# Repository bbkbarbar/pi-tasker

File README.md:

# Control center in living room
Based on Raspberry Pi Zero

#### Clients can get infos from:
###### - Environment:
 	- Air temperature
 	- Aquarium-water temperature
 	- Relative humidity (later)
###### - Internal status:
 	- Worker info (contains toDo items)
 	- Pwm output stated
 	- IO output states
###### - System infos
 	- CPU temp
 	- Memory info (later if needed)
 	- Free space (later if needed)
 	- Network logs (# of connections, etc.) (later if needed)

#### Temperature warnings can be sent via email for multiple recipient in case of:
  - temperature (in selected sensor) rises above specified limit
  - temperature (in selected sensor) drops below specified limit

Temperature warning rules described in [JSON file](https://github.com/bbkbarbar/pi-tasker/blob/master/onTarget/home_-_pi/taskerData/TempWarnings.json).

#### Client can control:
| Item           | Control type               | Scheduled | Sensor based control | Exceptional control | Src                      |
| :------------- | :------------------------: | :-------: | :------------------: | :-----------------: | :----------------------: |
| Airpump        | On/Off                     | X         | -                    | X                   | 230VAC                   |
| Filter         | On/Off                     | X         | -                    | X                   | 230VAC                   |
| Water heater   | On/Off                     | X         | X                    | X                   | 230VAC                   |
| Water cooler   | Gradual speed control (pwm)| X         | X                    | X                   | 230VAC->12VDC - 1ch pwm  |
| Light          | On/Off, 3ch RGB color      | X         | -                    | X                   | 230VAC->12VDC - 3ch pwm  |

Note: System can handle further pwm output (in fact unlimited number / just depends on how much devices do you have from [Serial PWM Driver](https://bbkbarbar.github.io/Serial_PWM_Driver_with_OLED)).

[For furher information follow t link](https://bbkbarbar.github.io/Serial_PWM_Driver_with_OLED/#further_channels)

#### Other outputs:
 - WebUI (show temperature infos and status infos of controller peripherials)
 - Temperature logs
 - System logs

## Used external tool(s):
 - Install Apache Webserver:
 ```
 sudo apt-get install apache2 -y
 ```

## Deployment
 - Copy content of onTarget folder to user's folder on target.
 - Run deploy script (deploy.sh)
 - Copy release to user's folder
 - run first with run.sh with name of copied release as parameter (./run.sh t102.jar)

## Wireing
  Planned connection modul, to make connection clean:
  
  Note: Pi Zero has some GND and VCC pins in GPIO port, but more external module need to get power from Pi. Previously I tried to give energy for a module from output of an other, but this makes the connections complex.<br>
  So I'm planning to create a "connector" module (something like above), to make connections clean and clear.

## ToDo list:
 - [ ] Cleanup files for easy deployment
 - [ ] Create "deploy script"

[Back to top](#top)

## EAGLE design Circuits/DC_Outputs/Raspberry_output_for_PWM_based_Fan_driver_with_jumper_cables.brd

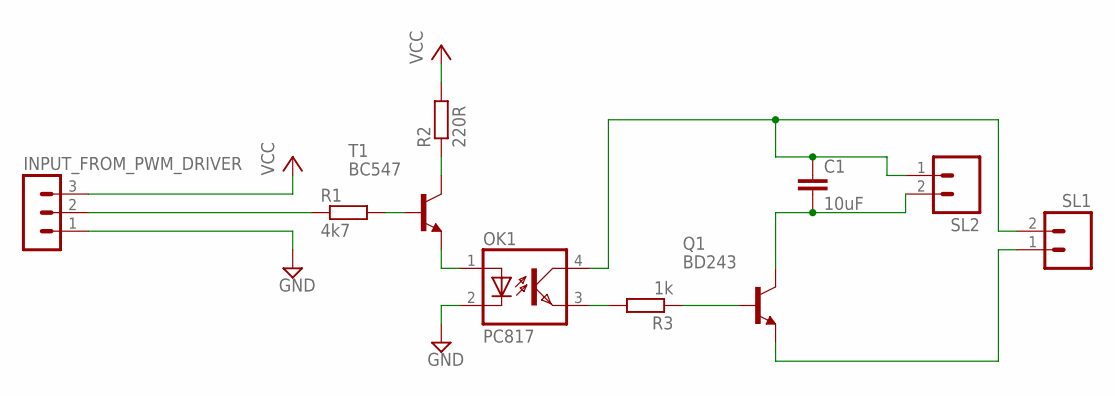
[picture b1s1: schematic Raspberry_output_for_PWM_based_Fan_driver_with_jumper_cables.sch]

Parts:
C1: 10uF; C2.5-5
INPUT_FROM_PWM_DRIVER: MA03-1
OK1: PC817; DIL04
Q1: BD243; TO220
R1: 4k7; 0207/10
R2: 220R; 0207/10
R3: 1k; 0207/10
SL1, SL2: MA02; 02PA
T1: BC547; TO92

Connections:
GND: INPUT_FROM_PWM_DRIVER.1, OK1.2 (C)
INPUT: INPUT_FROM_PWM_DRIVER.2, R1.1
INPUT_REGULATED_CURR_2_BASE: R1.2, T1.2 (B)
unnamed: R2.1, T1.3 (C)
OPTO_IN: OK1.1 (A), T1.1 (E)
OPTO_OUT_2_TR: OK1.3 (EMIT), R3.2
OUTPUT_N: C1.2, Q1.2 (C), SL2.2
SOURCE_N_0V: Q1.3 (E), SL1.1
SOURCE_P_12V: C1.1, OK1.4 (COL), SL1.2, SL2.1
TR_OUTPUT_BASE: Q1.1 (B), R3.1
VCC: INPUT_FROM_PWM_DRIVER.3, R2.2

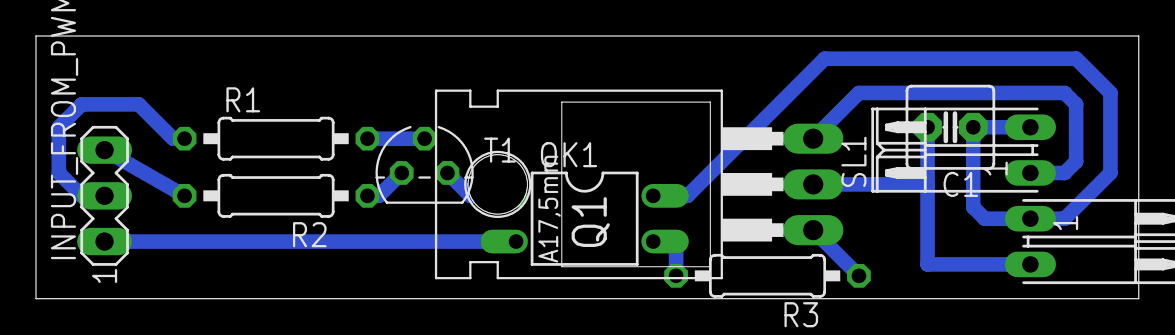
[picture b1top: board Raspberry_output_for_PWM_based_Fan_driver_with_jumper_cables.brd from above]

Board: 2 copper layers, 61.3 x 14.6 mm, 10 parts (0 on the bottom side), 11 nets.

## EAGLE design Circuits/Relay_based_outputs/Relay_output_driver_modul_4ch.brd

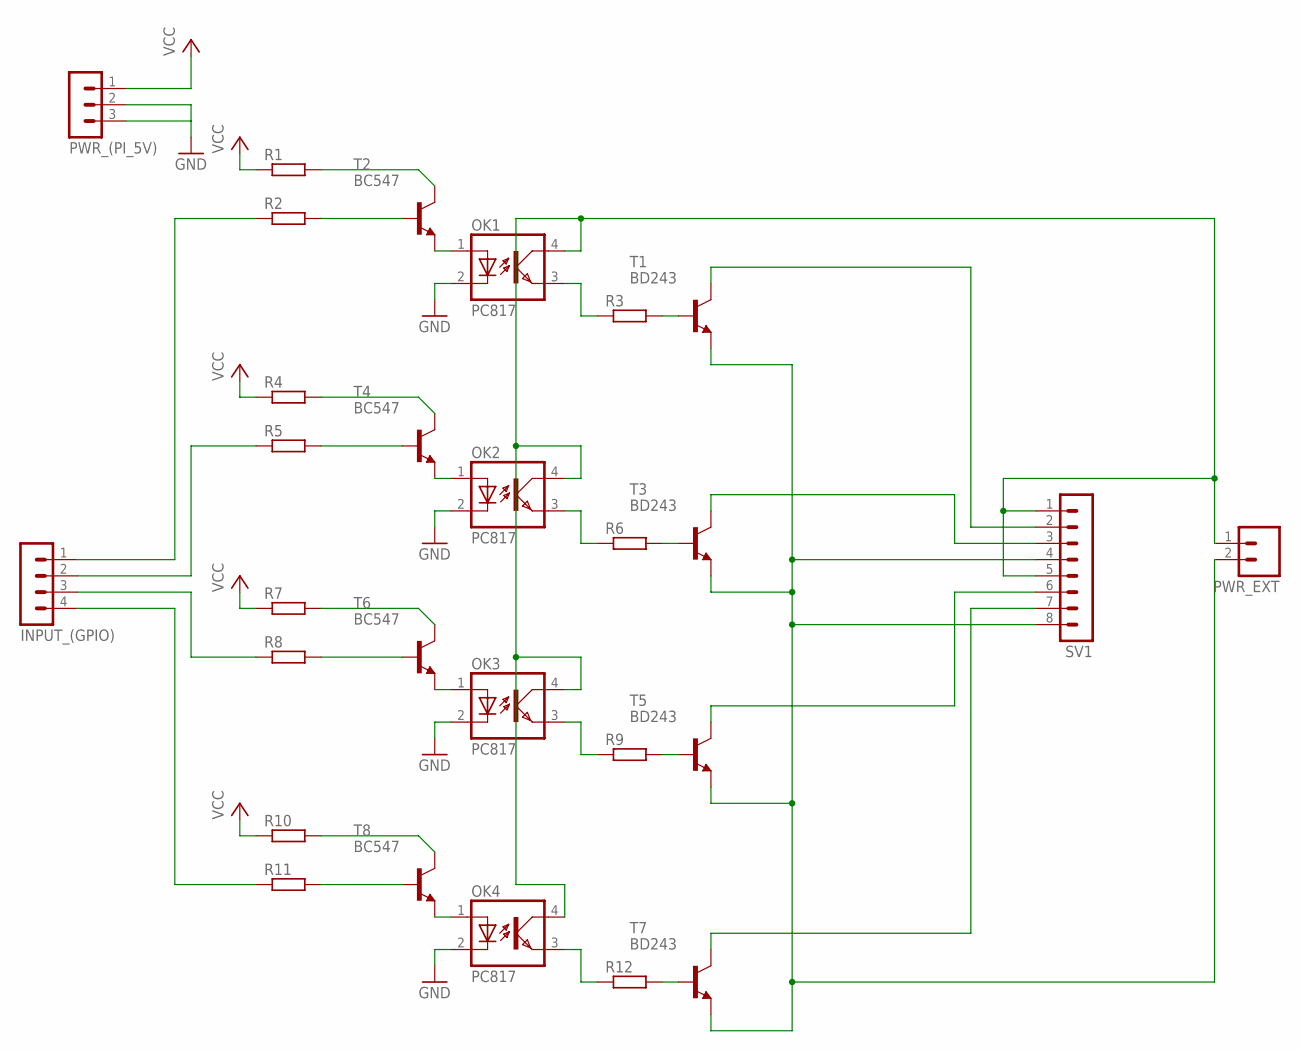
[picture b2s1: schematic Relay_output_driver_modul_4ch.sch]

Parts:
INPUT_(GPIO): MA04-1
OK1, OK2, OK3, OK4: PC817; DIL04
PWR_(PI_5V): MA03-1
PWR_EXT: MA02; 02PA
R1, R2, R3, R4, R5, R6, R7, R8, R9, R10, R11, R12: R-EU_0207/10; 0207/10
SV1: MA08-1
T1, T3, T5, T7: BD243; TO220
T2, T4, T6, T8: BC547; TO92

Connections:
GND: OK1.2 (C), OK2.2 (C), OK3.2 (C), OK4.2 (C), PWR_(PI_5V).2, PWR_(PI_5V).3
INPUT_1: INPUT_(GPIO).1, R2.1
INPUT_2: INPUT_(GPIO).2, R5.1
INPUT_3: INPUT_(GPIO).3, R8.1
INPUT_4: INPUT_(GPIO).4, R11.1
unnamed: OK1.1 (A), T2.1 (E)
unnamed: R3.2, T1.1 (B)
unnamed: OK1.3 (EMIT), R3.1
unnamed: R2.2, T2.2 (B)
unnamed: R1.2, T2.3 (C)
unnamed: OK2.1 (A), T4.1 (E)
unnamed: R6.2, T3.1 (B)
unnamed: OK2.3 (EMIT), R6.1
unnamed: R5.2, T4.2 (B)
unnamed: R4.2, T4.3 (C)
unnamed: OK3.1 (A), T6.1 (E)
unnamed: R9.2, T5.1 (B)
unnamed: OK3.3 (EMIT), R9.1
unnamed: R8.2, T6.2 (B)
unnamed: R7.2, T6.3 (C)
unnamed: OK4.1 (A), T8.1 (E)
unnamed: R12.2, T7.1 (B)
unnamed: OK4.3 (EMIT), R12.1
unnamed: R11.2, T8.2 (B)
unnamed: R10.2, T8.3 (C)
OUTPUT_1: SV1.2, T1.2 (C)
OUTPUT_2: SV1.3, T3.2 (C)
OUTPUT_3: SV1.6, T5.2 (C)
OUTPUT_4: SV1.7, T7.2 (C)
PWR_EXT_5V: OK1.4 (COL), OK2.4 (COL), OK3.4 (COL), OK4.4 (COL), PWR_EXT.1, SV1.1, SV1.5
PWR_EXT_GND: PWR_EXT.2, SV1.4, SV1.8, T1.3 (E), T3.3 (E), T5.3 (E), T7.3 (E)
VCC: PWR_(PI_5V).1, R1.1, R4.1, R7.1, R10.1

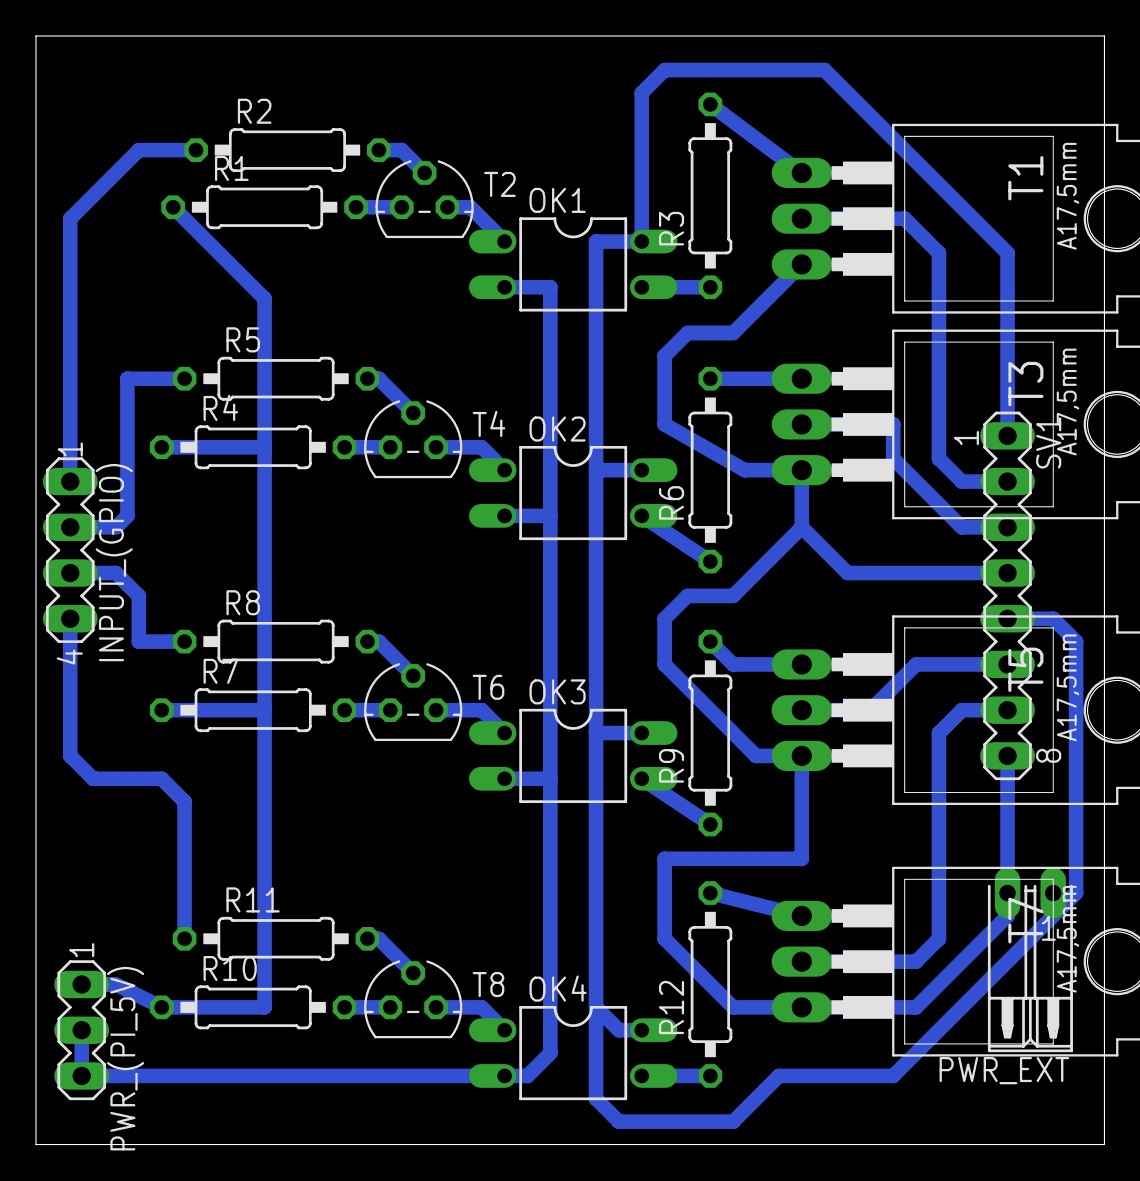
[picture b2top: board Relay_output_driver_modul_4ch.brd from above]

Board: 2 copper layers, 59.4 x 61.6 mm, 28 parts (0 on the bottom side), 32 nets.

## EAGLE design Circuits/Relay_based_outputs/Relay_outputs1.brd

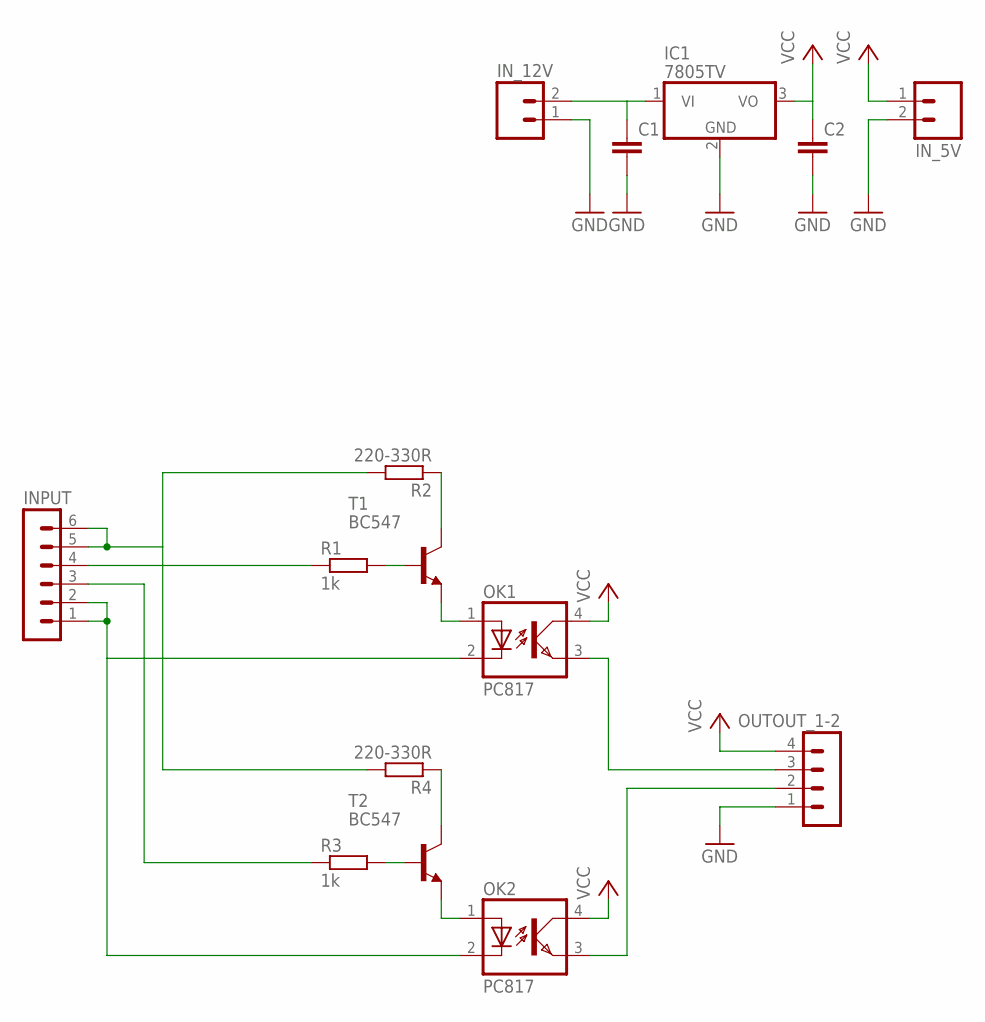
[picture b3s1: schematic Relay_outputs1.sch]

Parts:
C1, C2: C-EU050-024X044; C050-024X044
IC1: 7805TV; TO220V
INPUT: MA06-1
IN_5V, IN_12V: MA02; 02PA
OK1, OK2: PC817; DIL04
OUTOUT_1-2: MA04-1
R1, R3: 1k; 0207/10
R2, R4: 220-330R; 0207/10
T1, T2: BC547; TO92

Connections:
DC_IN: C1.1, IC1.1 (VI), IN_12V.2
GND: C1.2, C2.2, IC1.2 (GND), IN_5V.2, IN_12V.1, OUTOUT_1-2.1
INPUT_REGULATED_CURR_2_BASE: R1.2, T1.2 (B)
INPUT_REGULATED_CURR_2_BASE1: R3.2, T2.2 (B)
unnamed: R2.1, T1.3 (C)
unnamed: R4.1, T2.3 (C)
OPTO_IN: OK1.1 (A), T1.1 (E)
OPTO_IN1: OK2.1 (A), T2.1 (E)
OUT1: OK1.3 (EMIT), OUTOUT_1-2.3
OUT2: OK2.3 (EMIT), OUTOUT_1-2.2
PI_GND: INPUT.1, INPUT.2, OK1.2 (C), OK2.2 (C)
PI_OUT_1: INPUT.4, R1.1
PI_OUT_2: INPUT.3, R3.1
PI_VCC: INPUT.5, INPUT.6, R2.2, R4.2
VCC: C2.1, IC1.3 (VO), IN_5V.1, OK1.4 (COL), OK2.4 (COL), OUTOUT_1-2.4

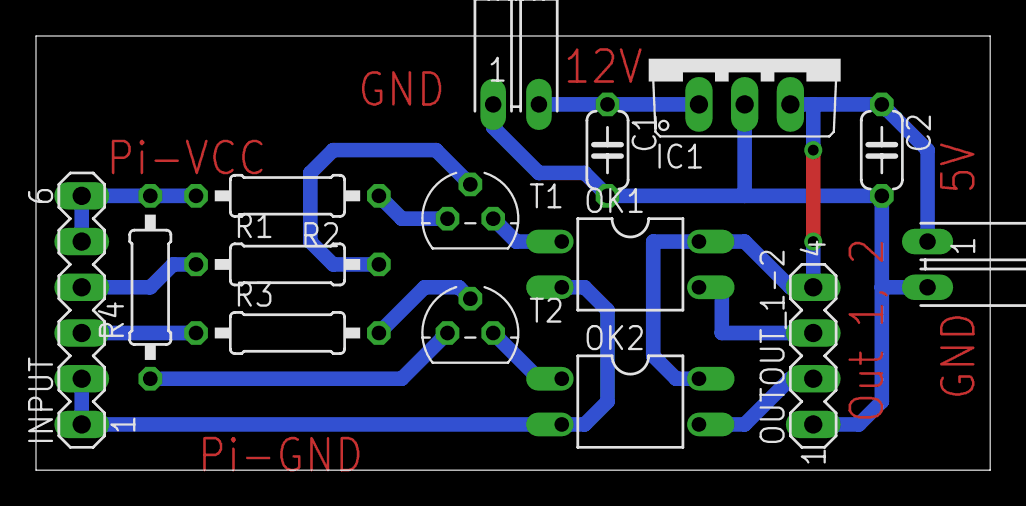
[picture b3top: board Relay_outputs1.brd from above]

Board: 2 copper layers, 53.0 x 24.1 mm, 15 parts (0 on the bottom side), 15 nets.

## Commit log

2016-08-14 commit to dedicated repo
2016-08-14 Refactor
2016-08-14 GitIgnore added
2016-08-14 copy files from old repo
2016-08-14 Communication classed refactored
2016-08-14 Works as a maven project
2016-08-16 TempControllers loaded from Json
2016-08-18 HotFix, need to find problem
2016-08-24 Add circuit design for detached low current relay-module controller
2016-08-27 Minimal modifications
2016-08-30 Create final circuit design for Fan controller and relay driver modules
2016-08-30 Circuit and PCB design added for fan driver module
    Based on jumper-cable -connections
2016-08-30 only test-only modification - removed
2016-09-04 Get IO state -function added (b#82)
2016-09-05 Can receive "get state of" commands, But not send response yet.
2016-09-05 Pinput config can handle "reversed IO" -like configurations
2016-09-05 Function: get state of ... seems OK except the "reversed" feature
2016-09-05 Get state of function mainly works
    except the "Reverse" function
2016-09-05 Get state of ... function seems OK
2016-09-05 Add feature: get state of ...
2016-09-05 Get state of ... works (with reversed IO outputs too)
2016-09-05 Get state of .. WORKS properly (with reversed output too)
2016-09-05 Warnings fixed.
2016-09-06 Use StateMsg object as response of "get state of ..." request
2016-09-06 SafetySwichOff - added (partly done)
2016-09-06 Response of "get state of ..." request sent as StatusMsg object
2016-09-08 Fan boost start parameters load from baseconfig
2016-09-08 Add parameters of fan boost start -function to base.conf
2016-09-09 Json formatting
2016-09-09 TempController related config file udated
2016-09-10 Update project specification
2016-09-11 Worker can get list of toDoItems
2016-09-11 TempWarnings (mulitple) can be loaded from 1 JSON file.
2016-09-11 Add sample JSON for TempWarnings
2016-09-11 TempWarning JSON file show as link
2016-09-11 Remove old test-only file
2016-09-11 bug fix
2016-09-11 Function added: getDirectionAsHuman
2016-09-11 Direction can described "as human" (below/above) instead of -1/+1.
2016-09-11 Use human-readable direction and observedSensor values
2016-09-11 TempControl's output does not contains "RuleID" if there is only 1 rule.
2016-09-11 Add sample for tempWarning.json
2016-09-12 Do not show RuleID if there is only 1 rule
2016-09-12 Debug level changed to INFO.
2016-09-12 Add EventLogger entries
2016-09-12 Clean commented parts
2016-09-12 Backup of -before cleaning- Tasker.java
2016-09-12 EventLogger get "Turn Off (heater/cooler)" event.
2016-09-14 Add function: getHumidityOnly (with mocked reader script)
2016-09-14 Can read and send humidity value
2016-09-14 Read humidity (with mock yet)
2016-09-19 Pinout config can saved as JSON.
2016-09-22 Works from ini conf, can test json conf
2016-09-28 HeaterLogItem added.
2016-09-30 HeaterLogItem added with tests
2016-10-01 Remove unnecessary code parts.
2016-10-01 Rename HeaterLog -> UseageLog
2016-10-01 Add UseageLog and UseageLogItem classes
2016-10-01 Package refactor only
2016-10-01 Name refactor
2016-10-01 TempController can provide energyConsumptionInfo if UsageLog added.
2016-10-01 Add energyConsumptionInfo
2016-10-02 Heater usage log seems OK.
2016-10-24 Reading humidity works fine.
2016-10-29 Map to humidity reader script changed to mocked.
2016-11-25 Add json to define timed output events
2016-11-25 Add feature for scheduled output events
2016-11-25 Add some log info
2016-11-28 Fix issue: multiple pwm channel update
2016-11-28 update JSON
2016-11-29 b96 - working version
2016-12-17 Try to solve bug in OutputState's constuctor
2017-02-10 Set theme jekyll-theme-slate
2017-02-27 Remove unsused lines
2017-02-27 Pack eagle files as .zip
2017-02-28 Minimal refactor near external resouces
2017-03-01 Add currently used external resources
2017-03-01 Pack contained .js files as .zip
2017-03-02 Fix invalide JSON
2017-03-02 remove temporary test lines
2017-03-09 Update filenames according to live version
2017-03-10 Decrease log level of humidity reading - t99
2017-03-24 live/io.py renamed because of Python-Serial-ISSUE
2017-03-24 Disable temperature related ToDoItems
2017-03-24 get LogLevels from JSON; temperature reading mocked.
2017-03-25 PWM outputs works fine with Serial-PWM-Driver
2017-03-25 Add misc files for Pi-user's folder
2017-03-25 Add instruction for install used webserver service
2017-03-25 Add Releases folder to store last builds
2017-03-25 Move file to appropira folder
2017-03-25 Add ToDo list
2017-03-25 update onBoard taskDate folder
2017-03-25 cleanup file-structure
2017-03-25 Add deploy script
2017-03-26 Update light values (sunrise / sunset)
2017-03-27 DayLightSavingTime -issue of ScheduledOutputEvent solved. - Need to test on target device
2017-03-27 Add script for cloning deployment content only
2017-03-27 DayLightSavingTime -issue of ScheduledOutputEvent solved. - Need to test
2017-03-27 Reaf logLevels from multi-level JSON config
2017-03-27 Add skeleton of mail.config
2017-03-27 Add missing config file
2017-03-27 Add latest build
2017-03-27 DayLightTimeZone Issue solved
2017-03-27 Restore outputConfig.json
2017-03-28 Current running version
2017-03-28 Add error-logs for read-int-from-json parts, to find the source of problem
2017-03-29 Modify pom for build runnable jar with Maven install
2017-03-29 Output config reading issue solved
2017-03-29 Add exception handling and readable log messages when IOLogger, EventLogger or Mailer can not be initialized due missing config
2017-03-29 Some fixing + Start to implement using any value from configJSON
2017-03-29 Tests added for reading single- and multi-level configValues from ConfigJSON
2017-03-29 Add sample JSONs for testing and for normal sample
2017-03-29 Config can read values from multi-level JSON-path
2017-03-29 Config can be loaded from JSON
2017-03-29 Add unnamed build to gitIgnore
2017-03-29 Fix typos
2017-03-29 Config values can be loaded from config JSON
2017-03-29 Read configs from JSON works - b107
2017-03-29 Rename last build
2017-03-30 Add sample for scheduledOutputEvents.json
2017-03-30 Update scheduled output events to create sunset of fishtank
2017-03-30 Add calculator to create sunset/sunrise easily
2017-03-30 Refactor since there is no t(String) method in Logger
2017-03-30 Add javadoc for getConfig..() methods
2017-03-30 Typo fix
2017-03-30 Refactor config loading, use config elements from JSON
2017-03-31 BuildNumber moved to a separated class for clear git history
2017-03-31 TempLogger instances reads their parameters from config JSON
2017-03-31 Read path for IO and Event logs from config JSON
2017-03-31 WebUI can read temperature log feed and write own log for different log folder. It uses the temp_logger.path_for_logfile parameter for the feed
2017-03-31 App can run again on local device too
2017-03-31 Update sample JSONs
2017-03-31 Initialize main Logger instance with parameters from baseConfig.json
2017-03-31 Default PATH_FOR_LOG_FOLDER will works on target and on dev environment too
2017-03-31 Implament function guaranteePathSeparatorAtEndOf to make code cleaner
2017-03-31 Guarantee slash at the end of folder path moved to FileHandler
2017-03-31 Method getInt() implemented in Config class
2017-03-31 Parameter: fan start boost time in ms moved to baseConfig.json
2017-03-31 Refactor: Config.getConfig.. -> Config.get...
2017-03-31 All parameters from old base.conf moved to baseConf.json
2017-03-31 All config parameters loaded from baseConf.json
2017-03-31 Clean onTarget taskerData folder. Removed non-used config files
2017-03-31 Refactor, remove uneccesarry lines
2017-03-31 Refactor methods what uses the old base.conf
2017-03-31 Solve warnings
2017-03-31 Heater's energy consumption can be loaded from baseConfig.json; We can read Floats and Doubles from config JSON
2017-03-31 Add heater's energy consumption as part of baseConfig
2017-03-31 Update mvn site with project infos
2017-03-31 update since scheudled RGB lighting works fine
2017-03-31 Filename for basic temperature log can be loaded from config JSON
2017-03-31 Can read Objects from any JSON like from baseConfig.json
2017-03-31 Add missing log-case in tempWarning class
2017-03-31 Path of live web content loaded from config json
2017-03-31 Mailer gives more reable log messages if it can not be initialized
2017-03-31 Can run n dev-env, need to try out on target device
2017-04-01 Add funciton fixPathSeparator (for current OS)
2017-04-02 Normalize log-levels for read pinout config -funciton
2017-04-02 Everithing seems OK.
2017-04-02 Rename String-type Config.get(..) functions as getString(..)
2017-04-02 Implement function: Config.getArray(..) to read JSONArray from config.json
2017-04-02 Add unitTest for readOutputConfigFromIni(..)
2017-04-02 OutputConfig with name can build from JSON object from config.json
2017-04-03 Config.readOutputConfigFromJson(..) implemented.
2017-04-03 Read OutputConfig elements from baseConfig.json
2017-04-03 Remove unused functions
2017-04-03 Fix warnings
2017-04-03 Implement missing warning messages.
2017-04-03 Minor javadoc changes
2017-04-12 Add design for module connector unit
2017-04-12 Update module connector unit
2017-04-12 Add printable module connection diagram
2017-04-13 Add plan of connector module
2017-06-14 b113: Add new python scipt for read water temperature at least.
2017-06-17 Enable toDo items what were disabled due temperature sensors broken
2017-06-19 Remove measurement problem results (0.0C) from logs
2017-06-23 Add new TempLogger ToDoItem for logging cooler useage as % in a csv file
2017-06-23 Fix in b115
2017-06-24 Issue fixed: temp and cooler log csv does not contains 0.0C water temperature (what coused by measurement problem)
2017-07-20 Reduce green component in lighting parameters
2019-10-03 ToDoItem for dispatch data from IoT device to TS
    Add ToDoItem for dispatch data from IoT device to ThingSpeak
2019-10-11 IoT dispatch -> TS works fine
2019-10-15 Add TSUpdater object
    .. can handle multiple inputs from different IoT devices and send all data to Same ThingSpeak channel
2020-10-13 Bump junit from 4.11 to 4.13.1 in /TaskerApp
    Bumps [junit](https://github.com/junit-team/junit4) from 4.11 to 4.13.1.
    - [Release notes](https://github.com/junit-team/junit4/releases)
    - [Changelog](https://github.com/junit-team/junit4/blob/main/doc/ReleaseNotes4.11.md)
    - [Commits](https://github.com/junit-team/junit4/compare/r4.11...r4.13.1)
2022-06-29 Bump poi from 4.1.0 to 4.1.1 in /TaskerApp
    Bumps poi from 4.1.0 to 4.1.1.
    ---
    updated-dependencies:
    - dependency-name: org.apache.poi:poi
    dependency-type: direct:production
    ...
